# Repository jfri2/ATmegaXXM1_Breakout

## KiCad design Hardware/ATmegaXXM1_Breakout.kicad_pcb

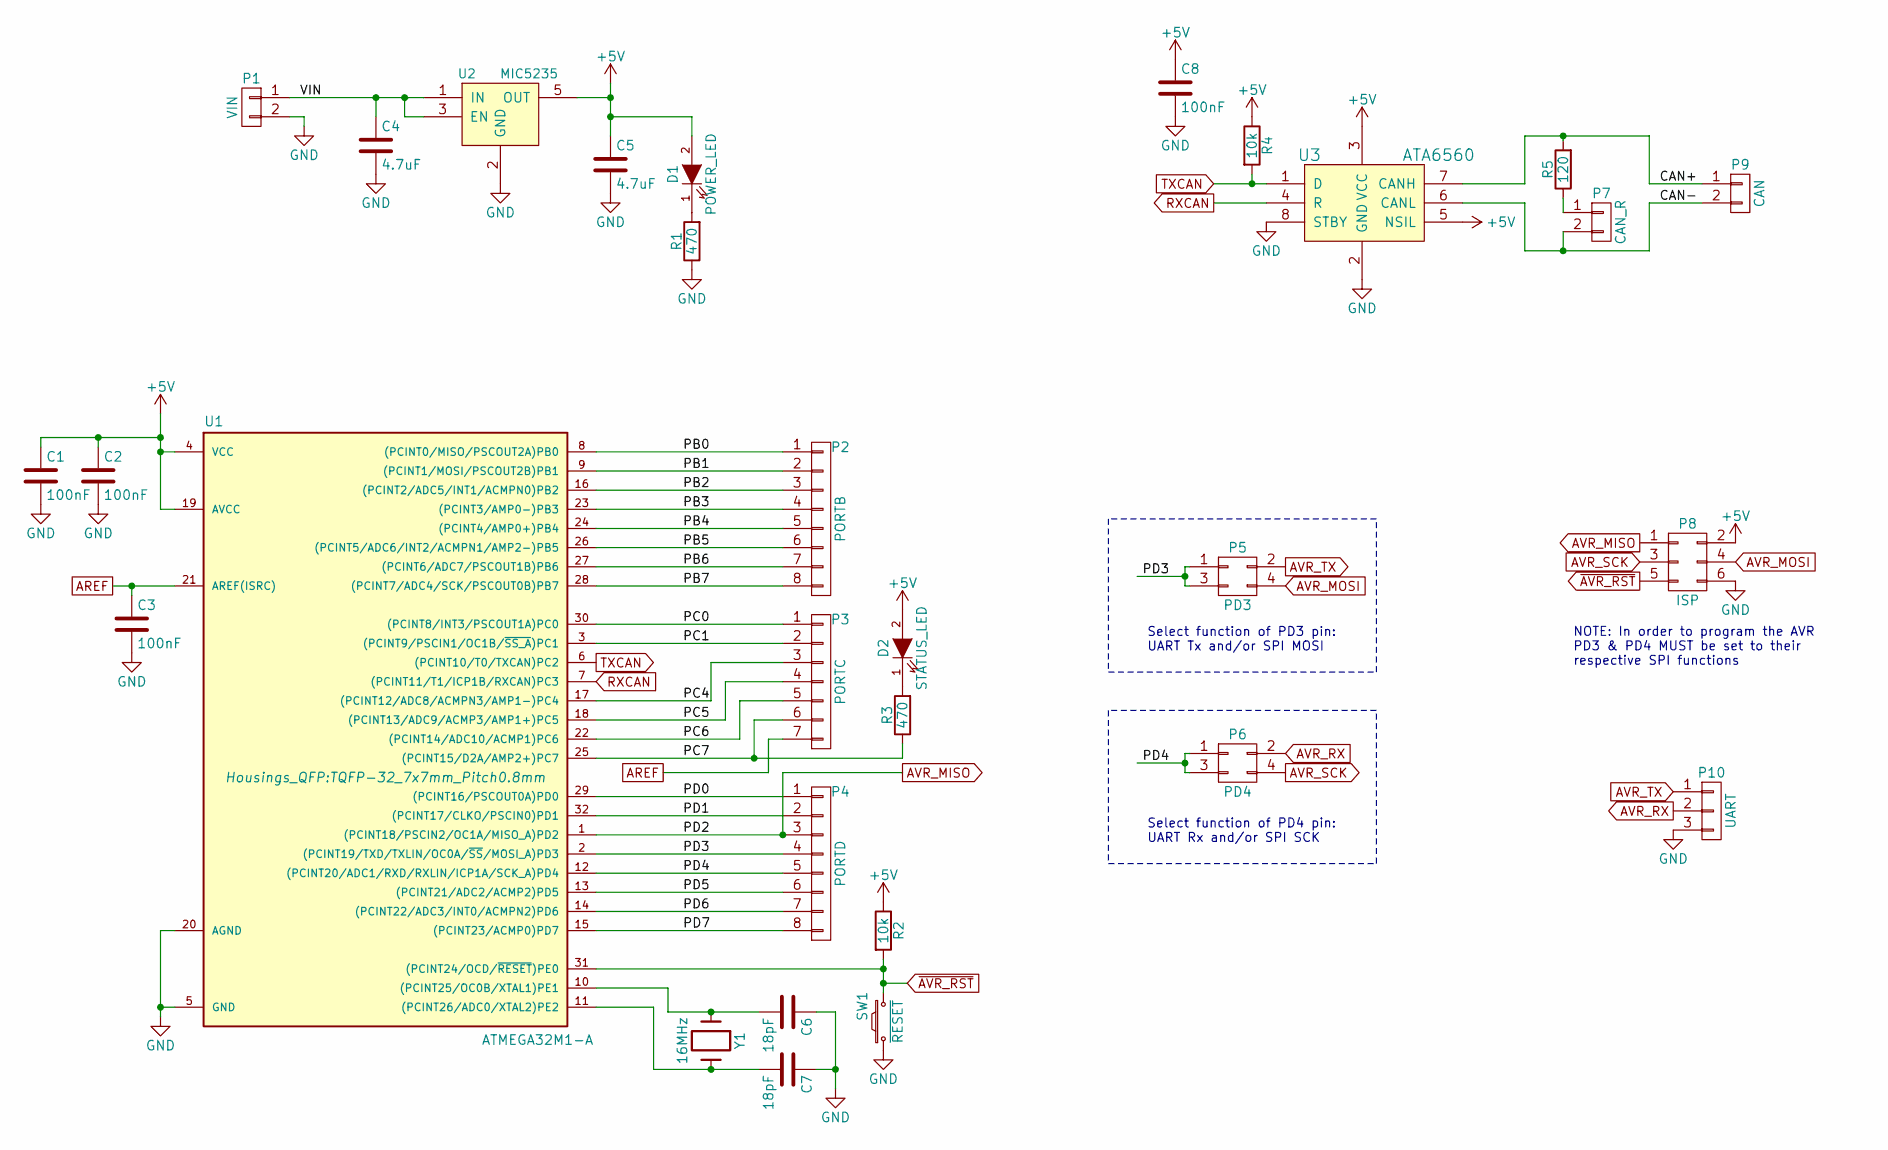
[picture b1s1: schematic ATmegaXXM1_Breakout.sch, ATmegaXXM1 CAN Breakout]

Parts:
C1, C2, C3, C8: 100nF; C_0805
C4, C5: 4.7uF; C_0805
C6, C7: 18pF; C_0805
D1: POWER_LED; LED_0805
D2: STATUS_LED; LED_0805
P1: VIN; 2x01_ScrewTerm
P2: PORTB; Pin_Header_Straight_1x08
P3: PORTC; Pin_Header_Straight_1x07
P4: PORTD; Pin_Header_Straight_1x08
P5: PD3; Pin_Header_Straight_2x02
P6: PD4; Pin_Header_Straight_2x02
P7: CAN_R; Pin_Header_Straight_1x02
P8: ISP; Pin_Header_Straight_2x03
P9: CAN; 2x01_ScrewTerm
P10: UART; Pin_Header_Straight_1x03
R1, R3: 470; R_0805
R2, R4: 10k; R_0805
R5: 120; R_1206
SW1: ~RESET; SW_SPST_EVQPE1
U1: ATMEGA32M1-A; TQFP-32_7x7mm_Pitch0.8mm
U2: MIC5235; SOT-23-5
U3: ATA6560; SOIC-8_3.9x4.9mm_Pitch1.27mm
Y1: 16MHz; Crystal_HC49-SD_SMD

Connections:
+5V: C1.1, C2.1, C5.1, C8.1, D1.2 (A), D2.2 (A), P8.2, R2.1, R4.1, U1.4 (VCC), U1.19 (AVCC), U2.5 (OUT), U3.3 (VCC), U3.5 (NSIL)
/CAN+: P9.1, R5.2, U3.7 (CANH)
/CAN-: P7.2, P9.2, U3.6 (CANL)
/PB0: P2.1, U1.8 ((PCINT0/MISO/PSCOUT2A)PB0)
/PB1: P2.2, U1.9 ((PCINT1/MOSI/PSCOUT2B)PB1)
/PB2: P2.3, U1.16 ((PCINT2/ADC5/INT1/ACMPN0)PB2)
/PB3: P2.4, U1.23 ((PCINT3/AMP0-)PB3)
/PB4: P2.5, U1.24 ((PCINT4/AMP0+)PB4)
/PB5: P2.6, U1.26 ((PCINT5/ADC6/INT2/ACMPN1/AMP2-)PB5)
/PB6: P2.7, U1.27 ((PCINT6/ADC7/PSCOUT1B)PB6)
/PB7: P2.8, U1.28 ((PCINT7/ADC4/SCK/PSCOUT0B)PB7)
/PC0: P3.1, U1.30 ((PCINT8/INT3/PSCOUT1A)PC0)
/PC1: P3.2, U1.3 ((PCINT9/PSCIN1/OC1B/~SS_A~)PC1)
/PC4: P3.3, U1.17 ((PCINT12/ADC8/ACMPN3/AMP1-)PC4)
/PC5: P3.4, U1.18 ((PCINT13/ADC9/ACMP3/AMP1+)PC5)
/PC6: P3.5, U1.22 ((PCINT14/ADC10/ACMP1)PC6)
/PC7: P3.6, R3.1, U1.25 ((PCINT15/D2A/AMP2+)PC7)
/PD0: P4.1, U1.29 ((PCINT16/PSCOUT0A)PD0)
/PD1: P4.2, U1.32 ((PCINT17/CLKO/PSCIN0)PD1)
/PD3: P4.4, P5.1, P5.3, U1.2 ((PCINT19/TXD/TXLIN/OC0A/~SS~/MOSI_A)PD3)
/PD4: P4.5, P6.1, P6.3, U1.12 ((PCINT20/ADC1/RXD/RXLIN/ICP1A/SCK_A)PD4)
/PD5: P4.6, U1.13 ((PCINT21/ADC2/ACMP2)PD5)
/PD6: P4.7, U1.14 ((PCINT22/ADC3/INT0/ACMPN2)PD6)
/PD7: P4.8, U1.15 ((PCINT23/ACMP0)PD7)
/VIN: C4.1, P1.1, U2.1 (IN), U2.3 (EN)
AVR_MISO: P4.3, P8.1, U1.1 ((PCINT18/PSCIN2/OC1A/MISO_A)PD2)
AVR_MOSI: P5.4, P8.4
AVR_RX: P6.2, P10.2
AVR_SCK: P6.4, P8.3
AVR_TX: P5.2, P10.1
unnamed: C6.2, U1.10 ((PCINT25/OC0B/XTAL1)PE1), Y1.1
unnamed: C7.2, U1.11 ((PCINT26/ADC0/XTAL2)PE2), Y1.2
unnamed: D1.1 (K), R1.2
unnamed: D2.1 (K), R3.2
unnamed: P7.1, R5.1
RXCAN: U1.7 ((PCINT11/T1/ICP1B/RXCAN)PC3), U3.4 (R)
TXCAN: R4.2, U1.6 ((PCINT10/T0/TXCAN)PC2), U3.1 (D)
~AVR_RST: P8.5, R2.2, SW1.2, U1.31 ((PCINT24/OCD/~RESET~)PE0)

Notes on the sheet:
Select function of PD4 pin: UART Rx and/or SPI SCK
Select function of PD3 pin: UART Tx and/or SPI MOSI
NOTE: In order to program the AVR PD3 & PD4 MUST be set to their respective SPI functions

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
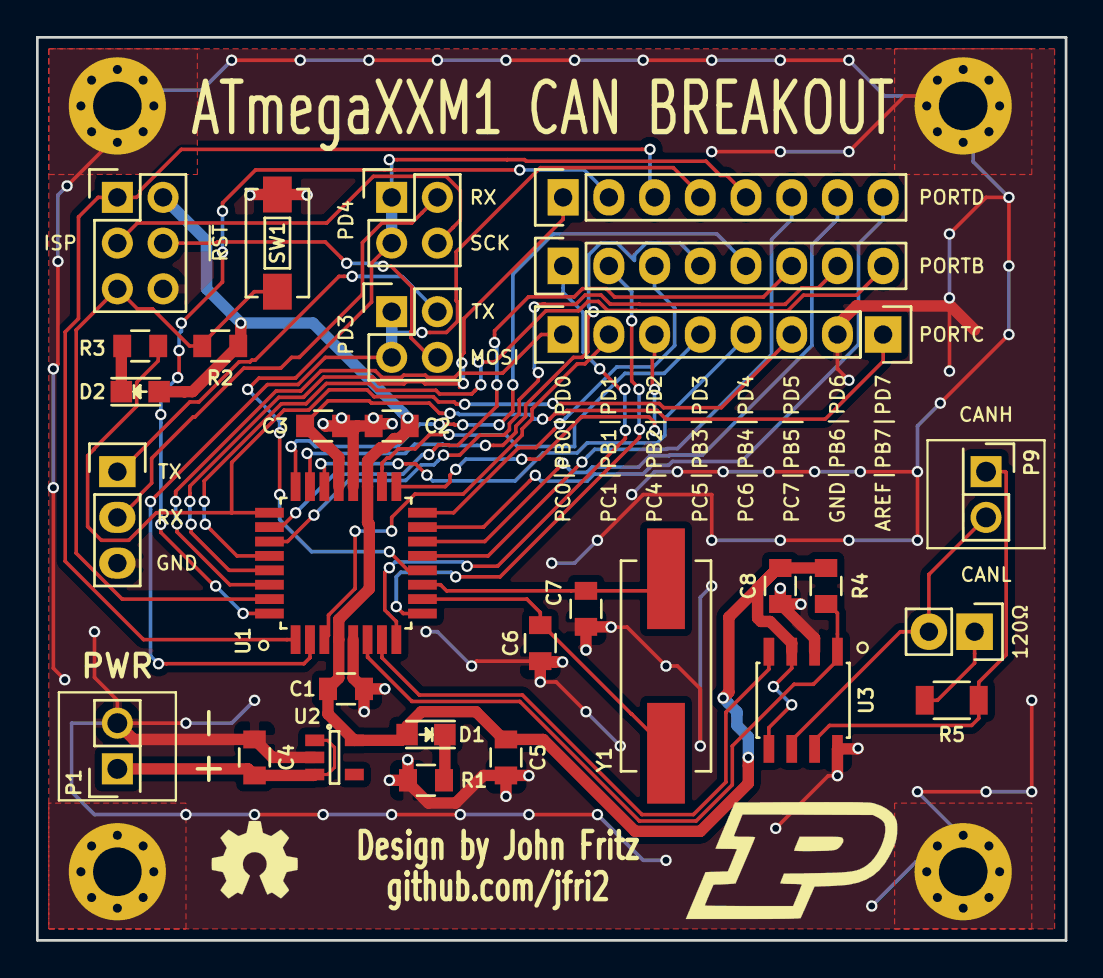
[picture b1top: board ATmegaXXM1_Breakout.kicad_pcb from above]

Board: 2 copper layers, 57.1 x 50.2 mm, 35 parts (0 on the bottom side), 40 nets.

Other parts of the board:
P11: AREF; Pin_Header_Straight_1x01
P12, P13, P14, P15: Mounting Hole; MountingHole_2.7mm_M2.5_Pad_Via

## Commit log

2016-10-03 :space_invader: Added .gitattributes & .gitignore files
2016-10-08 Finished rev 1.0 schematic & BOM
2016-10-08 Finished routing & added mouting holes
2016-10-08 Cleaned up PCB, added silkscreen & logos
2016-10-08 Generated Gerbers & PDFs of PCB, added 3D render image of PCB
2016-10-08 Fixed gnd fill on mounting holes & added vias connecting top & bottom gnd planes
2016-10-08 Rezipped gerbers
2016-10-08 Re-save of last commit
2016-10-09 Changed routing & removed via in pad. Regenerated gerbers
2016-11-10 I don't know what I did.
